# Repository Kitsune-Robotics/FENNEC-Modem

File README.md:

# The Fennec Modem

A **F**lexible **E**xperimental **N**etwork for **N**ovel **E**lectronic **C**ommunication!

Hello and thank you for looking in here!

APRN is a combined pairing of bell202 from packet radio, with SSTV and other more analog formats. While never widely adopted, I always had a strong affection for the strange format! The inspiration for this format was originally recorded [here.](https://web.archive.org/web/20080328040214/http://web.usna.navy.mil/~bruninga/aprntxt.html)

The Fennec Modem is designed with APRN in mind! But is in no means only limted to that one format, any AFSK or similar audio/soundcard mode radio should be possible with this board!

 - [x] APRN
 - [x] Packet
 - [ ] APRS
 - [ ] Other SSTV Formats

# Getting started

Clone this repo

```shell
git clone --recurse-submodules https://github.com/Kitsune-Robotics/FENNEC-Modem
```

# Thank You!

Without the resources from other hams on the internet, I don't know if i would ever get this project done!

https://github.com/handiko/Dorji-TX-Shield
http://squirrelengineering.com/arduino/dra818v-aprs-144-390mhz/

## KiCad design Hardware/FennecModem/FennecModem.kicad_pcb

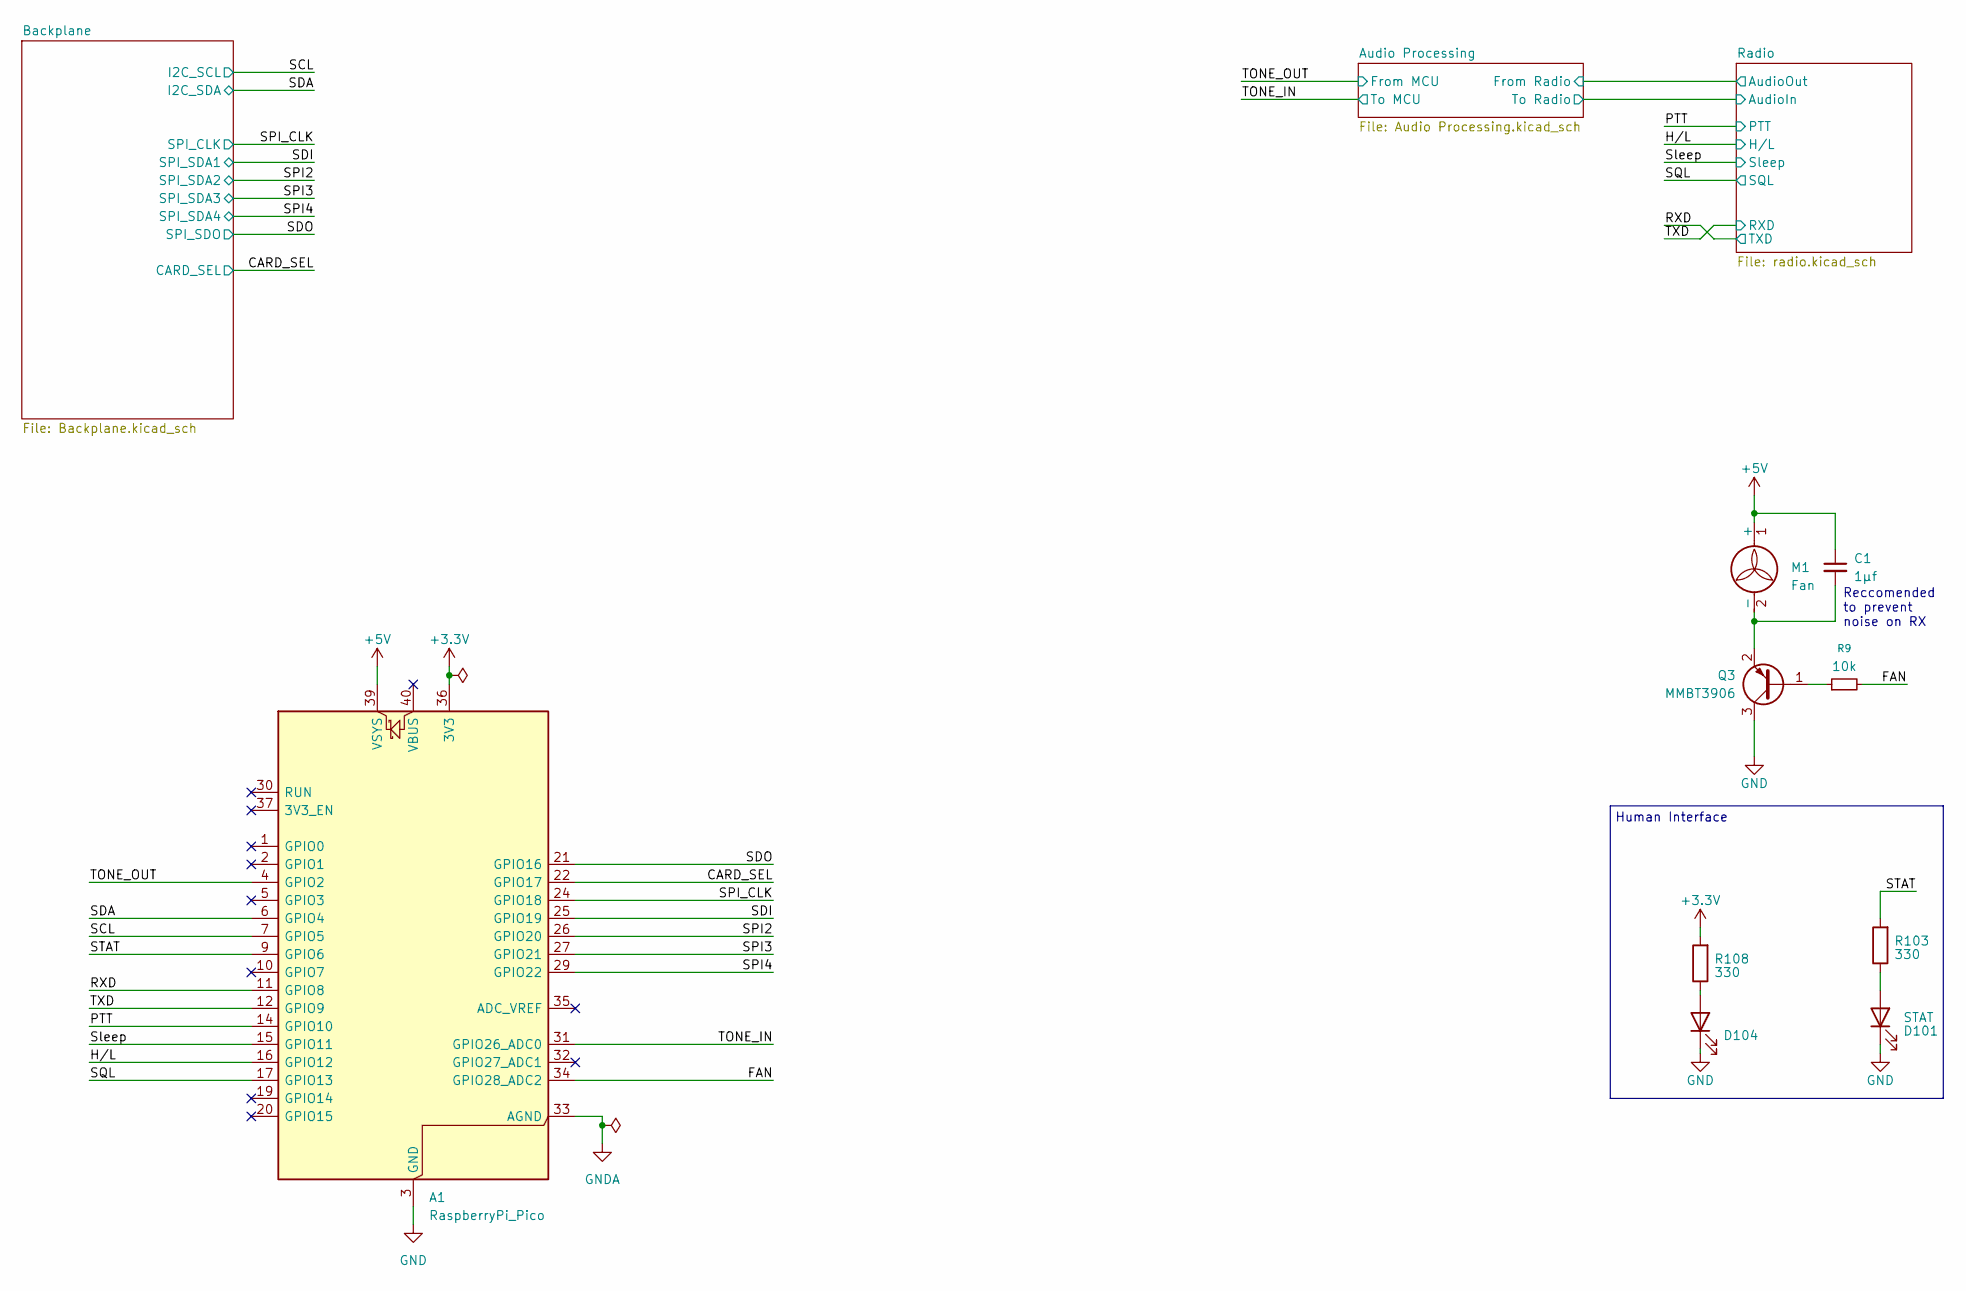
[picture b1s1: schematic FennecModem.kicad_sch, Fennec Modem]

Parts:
A1: RaspberryPi_Pico; RaspberryPi_Pico_Common_THT
C1: 1μf; C_0805_2012Metric
D101: STAT; LED_D3.0mm_Horizontal_O1.27mm_Z2.0mm
D104: PWR; LED_D3.0mm_Horizontal_O1.27mm_Z2.0mm
M1: Fan; JST_EH_B2B-EH-A_1x02_P2.50mm_Vertical
Q3: MMBT3906; SOT-23
R9: 10k; R_0805_2012Metric
R103, R108: 330; R_0805_2012Metric

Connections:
+3.3V: A1.36 (3V3), R108.2; also elsewhere on the board
+5V: A1.39 (VSYS), C1.1, M1.1 (+); also elsewhere on the board
/CARD_SEL: A1.22 (GPIO17); also elsewhere on the board
/FAN: A1.34 (GPIO28_ADC2), R9.2
/H/L: A1.16 (GPIO12); also elsewhere on the board
/PTT: A1.14 (GPIO10); also elsewhere on the board
/RXD: A1.11 (GPIO8); also elsewhere on the board
/SCL: A1.7 (GPIO5)
/SDA: A1.6 (GPIO4)
/SDI: A1.25 (GPIO19); also elsewhere on the board
/SDO: A1.21 (GPIO16); also elsewhere on the board
/SPI2: A1.26 (GPIO20); also elsewhere on the board
/SPI3: A1.27 (GPIO21); also elsewhere on the board
/SPI4: A1.29 (GPIO22); also elsewhere on the board
/SPI_CLK: A1.24 (GPIO18); also elsewhere on the board
/SQL: A1.17 (GPIO13); also elsewhere on the board
/STAT: A1.9 (GPIO6), R103.2
/Sleep: A1.15 (GPIO11); also elsewhere on the board
/TONE_IN: A1.31 (GPIO26_ADC0); also elsewhere on the board
/TONE_OUT: A1.4 (GPIO2); also elsewhere on the board
/TXD: A1.12 (GPIO9); also elsewhere on the board
GND: A1.3 (GND), A1.8 (GND), A1.13 (GND), A1.18 (GND), A1.23 (GND), A1.28 (GND), A1.38 (GND), D101.1 (K), D104.1 (K), Q3.3 (C); also elsewhere on the board
GNDA: A1.33 (AGND); also elsewhere on the board
unnamed: D101.2 (A), R103.1
unnamed: D104.2 (A), R108.1
unnamed: C1.2, M1.2 (-), Q3.2 (E)
unnamed: Q3.1 (B), R9.1

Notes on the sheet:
Reccomended to prevent noise on RX
Human Interface

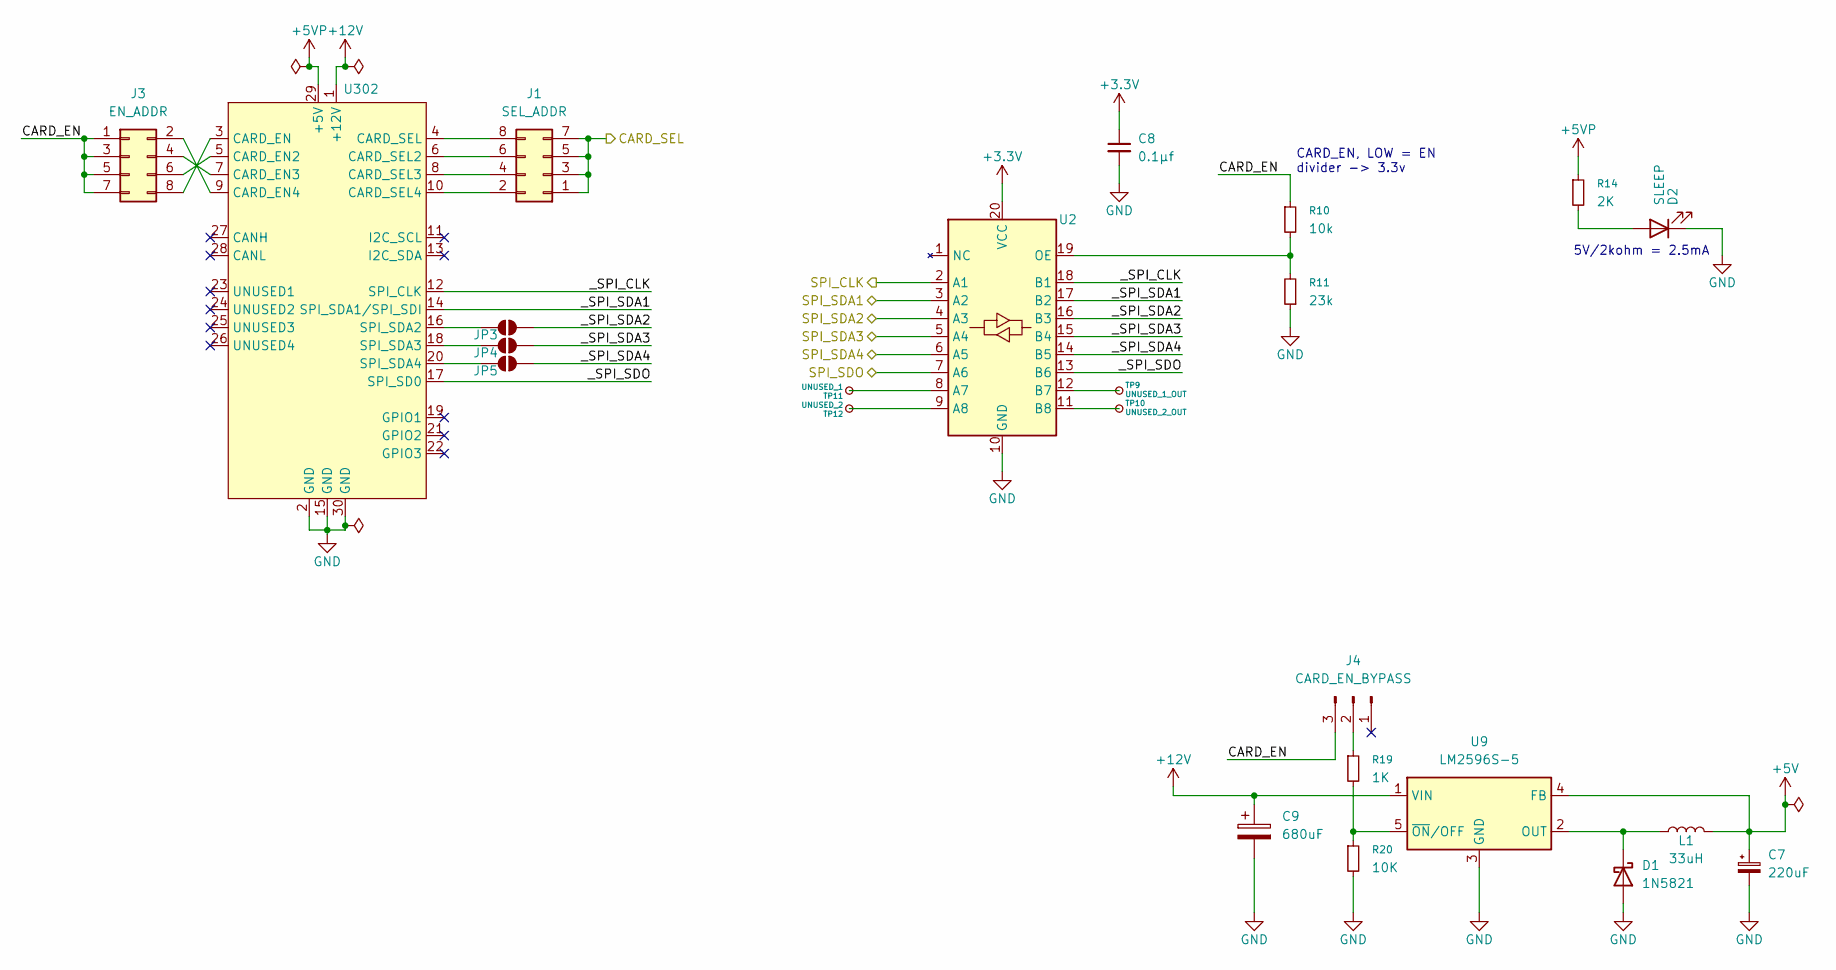
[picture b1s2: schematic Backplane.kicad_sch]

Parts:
C7: 220uF; CP_Radial_D5.0mm_P2.50mm
C8: 0.1μf; C_0805_2012Metric
C9: 680uF; CP_Radial_D10.0mm_P5.00mm
D1: 1N5821; D_DO-41_SOD81_P5.08mm_Vertical_AnodeUp; LCSC# C5295406
D2: SLEEP; LED_0805_2012Metric
J1: SEL_ADDR; PinHeader_2x04_P2.54mm_Vertical
J3: EN_ADDR; PinHeader_2x04_P2.54mm_Vertical
J4: CARD_EN_BYPASS; PinHeader_1x03_P2.54mm_Vertical
JP3, JP4, JP5: SolderJumper_2_Open; SolderJumper-2_P1.3mm_Open_TrianglePad1.0x1.5mm
L1: 33uH; L_6.3x6.3_H3
R10: 10k; R_0805_2012Metric
R11: 23k; R_0805_2012Metric
R14: 2K; R_0805_2012Metric
R19: 1K; R_0805_2012Metric
R20: 10K; R_0805_2012Metric
TP9: UNUSED_1_OUT; TestPoint_Bridge_Pitch2.0mm_Drill0.7mm
TP10: UNUSED_2_OUT; TestPoint_Bridge_Pitch2.0mm_Drill0.7mm
TP11: UNUSED_1; TestPoint_Bridge_Pitch2.0mm_Drill0.7mm
TP12: UNUSED_2; TestPoint_Bridge_Pitch2.0mm_Drill0.7mm
U2: SN74CBTLV3245A; SSOP-20_3.9x8.7mm_P0.635mm; LCSC# C2878923
U9: LM2596S-5; TO-263-5_TabPin3; LCSC# C116713
U302: Lewis_Card_Connector

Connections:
+3.3V: C8.1, U2.20 (VCC); also elsewhere on the board
+5V: C7.1, L1.2, U9.4 (FB); also elsewhere on the board
+5VP: R14.1, U302.29 (+5V)
+12V: C9.1, U9.1 (VIN), U302.1 (+12V)
/Backplane/CARD_EN: J3.1, J3.3, J3.5, J3.7, J4.3, R10.1
/Backplane/_SPI_CLK: U2.18 (B1), U302.12 (SPI_CLK)
/Backplane/_SPI_SDA1: U2.17 (B2), U302.14 (SPI_SDA1/SPI_SDI)
/Backplane/_SPI_SDA2: JP3.1 (A), U2.16 (B3)
/Backplane/_SPI_SDA3: JP4.1 (A), U2.15 (B4)
/Backplane/_SPI_SDA4: JP5.1 (A), U2.14 (B5)
/Backplane/_SPI_SDO: U2.13 (B6), U302.17 (SPI_SD0)
/CARD_SEL: J1.1, J1.3, J1.5, J1.7; also elsewhere on the board
/SDI: U2.3 (A2); also elsewhere on the board
/SDO: U2.7 (A6); also elsewhere on the board
/SPI2: U2.4 (A3); also elsewhere on the board
/SPI3: U2.5 (A4); also elsewhere on the board
/SPI4: U2.6 (A5); also elsewhere on the board
/SPI_CLK: U2.2 (A1); also elsewhere on the board
GND: C7.2, C8.2, C9.2, D1.2 (A), D2.1 (K), R11.1, R20.2, U2.10 (GND), U9.3 (GND), U302.2 (GND), U302.15 (GND), U302.30 (GND); also elsewhere on the board
unnamed: D1.1 (K), L1.1, U9.2 (OUT)
unnamed: D2.2 (A), R14.2
unnamed: J1.2, U302.10 (CARD_SEL4)
unnamed: J1.4, U302.8 (CARD_SEL3)
unnamed: J1.6, U302.6 (CARD_SEL2)
unnamed: J1.8, U302.4 (CARD_SEL)
unnamed: J3.2, U302.9 (CARD_EN4)
unnamed: J3.4, U302.7 (CARD_EN3)
unnamed: J3.6, U302.5 (CARD_EN2)
unnamed: J3.8, U302.3 (CARD_EN)
unnamed: J4.2, R19.1
unnamed: JP3.2 (B), U302.16 (SPI_SDA2)
unnamed: JP4.2 (B), U302.18 (SPI_SDA3)
unnamed: JP5.2 (B), U302.20 (SPI_SDA4)
unnamed: TP11.1, U2.8 (A7)
unnamed: TP12.1, U2.9 (A8)
unnamed: TP9.1, U2.12 (B7)
unnamed: TP10.1, U2.11 (B8)
unnamed: R10.2, R11.2, U2.19 (OE)
unnamed: R19.2, R20.1, U9.5 (~ON/OFF)

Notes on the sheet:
5V/2kohm = 2.5mA
CARD_EN, LOW = EN divider -> 3.3v

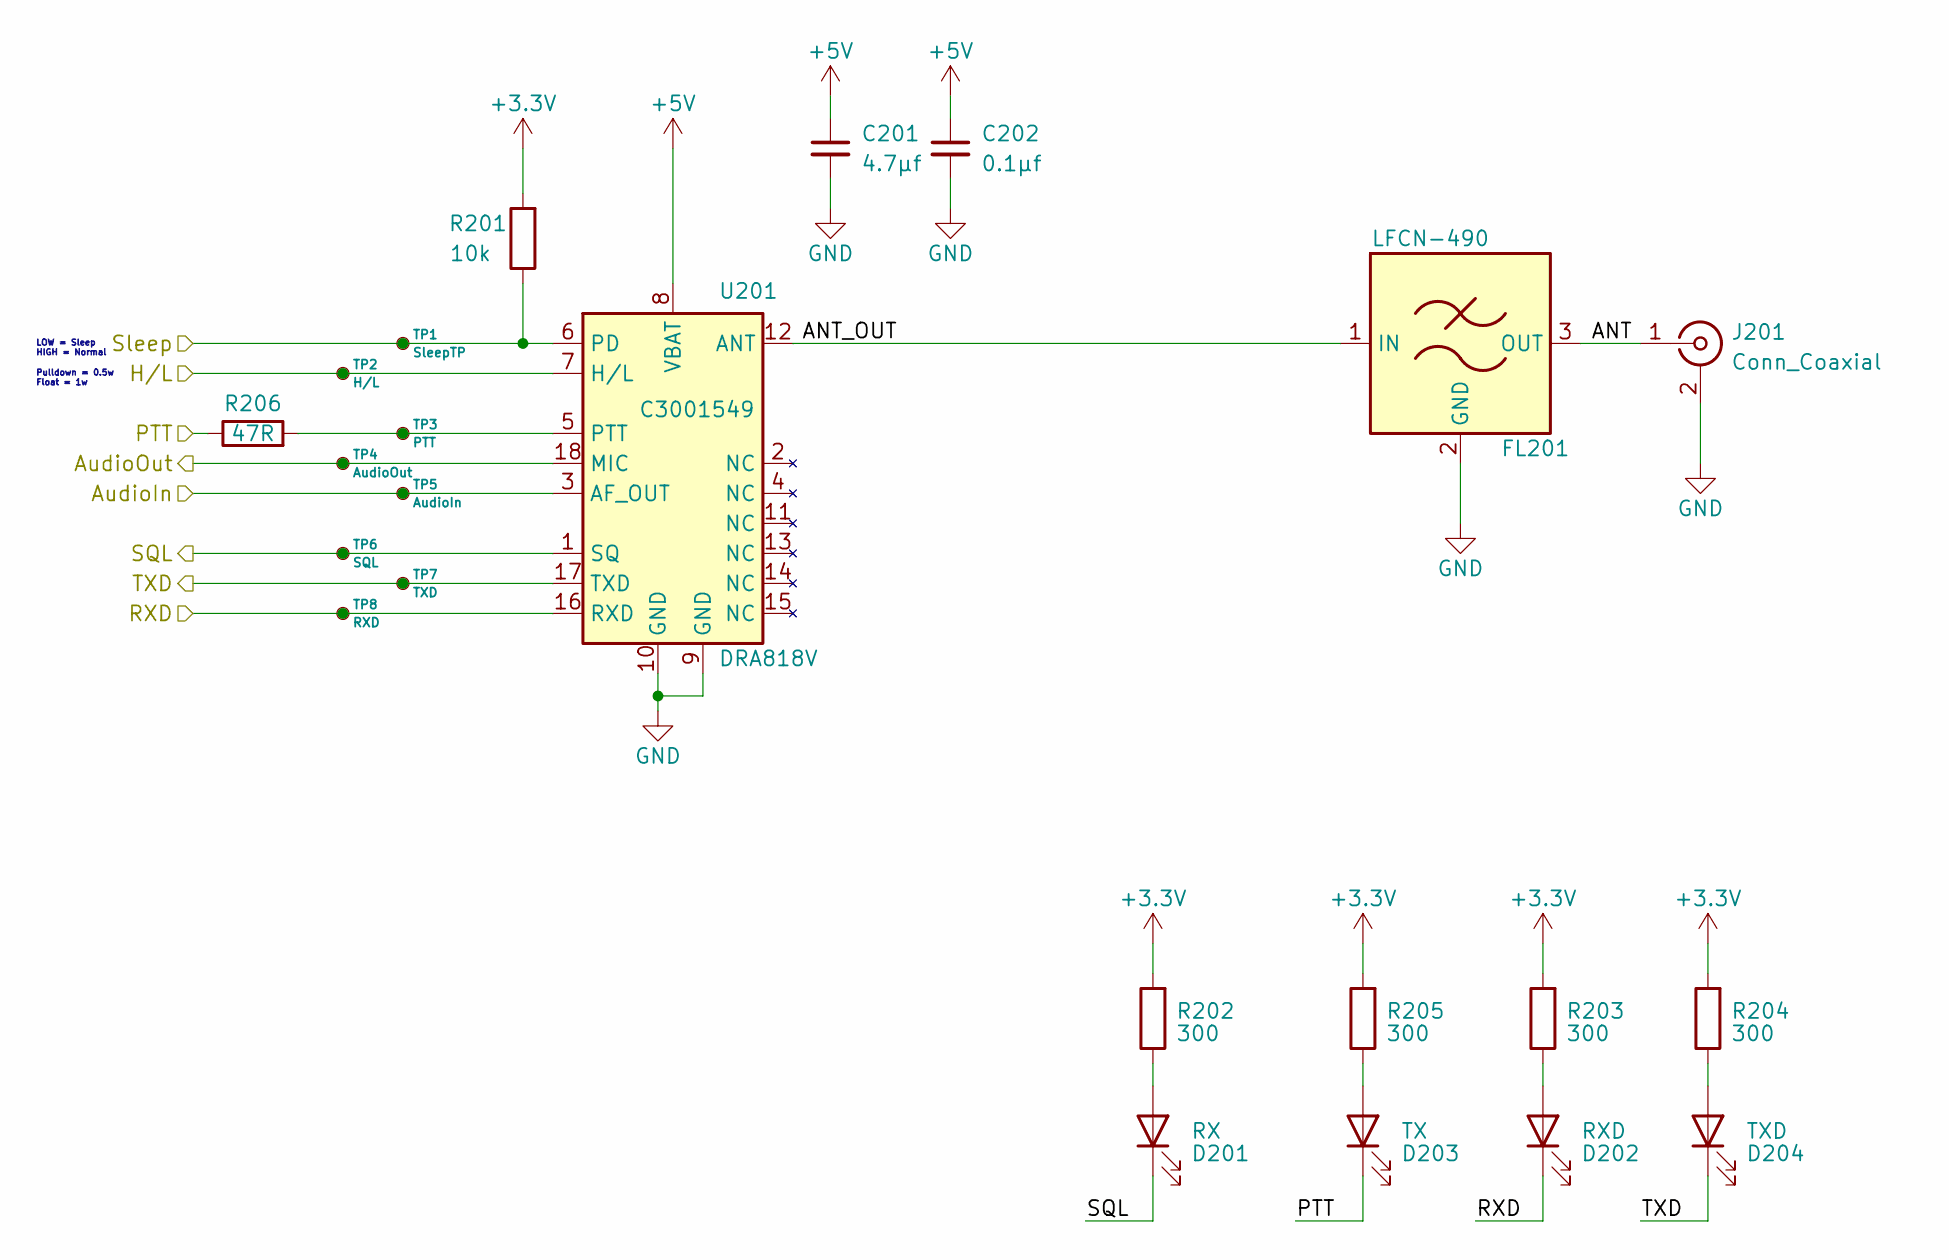
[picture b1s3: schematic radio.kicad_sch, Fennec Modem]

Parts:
C201: 4.7μf; C_0805_2012Metric
C202: 0.1μf; C_0805_2012Metric
D201: RX; LED_D3.0mm_Horizontal_O1.27mm_Z2.0mm
D202: RXD; LED_0805_2012Metric
D203: TX; LED_D3.0mm_Horizontal_O1.27mm_Z2.0mm
D204: TXD; LED_0805_2012Metric
FL201: LFCN-490; Filter_Mini-Circuits_FV1206
J201: Conn_Coaxial; SMA_Amphenol_132289_EdgeMount
R201: 10k; R_0805_2012Metric
R202, R203, R204, R205: 300; R_0805_2012Metric
R206: 47R; R_0805_2012Metric
TP1: SleepTP; TestPoint_Bridge_Pitch2.0mm_Drill0.7mm
TP2: H/L; TestPoint_Bridge_Pitch2.0mm_Drill0.7mm
TP3: PTT; TestPoint_Bridge_Pitch2.0mm_Drill0.7mm
TP4: AudioOut; TestPoint_Bridge_Pitch2.0mm_Drill0.7mm
TP5: AudioIn; TestPoint_Bridge_Pitch2.0mm_Drill0.7mm
TP6: SQL; TestPoint_Bridge_Pitch2.0mm_Drill0.7mm
TP7: TXD; TestPoint_Bridge_Pitch2.0mm_Drill0.7mm
TP8: RXD; TestPoint_Bridge_Pitch2.0mm_Drill0.7mm
U201: DRA818V; LCSC# C3001549

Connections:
+3.3V: R201.2, R202.2, R203.2, R204.2, R205.2; also elsewhere on the board
+5V: C201.1, C202.1, U201.8 (VBAT); also elsewhere on the board
/Audio Processing/From Radio: TP4.1, U201.18 (MIC); also elsewhere on the board
/Audio Processing/To Radio: TP5.1, U201.3 (AF_OUT); also elsewhere on the board
/H/L: TP2.1, U201.7 (H/L); also elsewhere on the board
/PTT: D203.1 (K), R206.1; also elsewhere on the board
/RXD: D204.1 (K), TP7.1, U201.17 (TXD); also elsewhere on the board
/Radio/ANT: FL201.3 (OUT), J201.1 (In)
/Radio/ANT_OUT: FL201.1 (IN), U201.12 (ANT)
/SQL: D201.1 (K), TP6.1, U201.1 (SQ); also elsewhere on the board
/Sleep: R201.1, TP1.1, U201.6 (PD); also elsewhere on the board
/TXD: D202.1 (K), TP8.1, U201.16 (RXD); also elsewhere on the board
GND: C201.2, C202.2, FL201.2 (GND), FL201.4 (GND), J201.2 (Ext), U201.9 (GND), U201.10 (GND); also elsewhere on the board
unnamed: D201.2 (A), R202.1
unnamed: D202.2 (A), R203.1
unnamed: D203.2 (A), R205.1
unnamed: D204.2 (A), R204.1
unnamed: R206.2, TP3.1, U201.5 (PTT)

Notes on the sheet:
Pulldown = 0.5w Float = 1w
LOW = Sleep HIGH = Normal

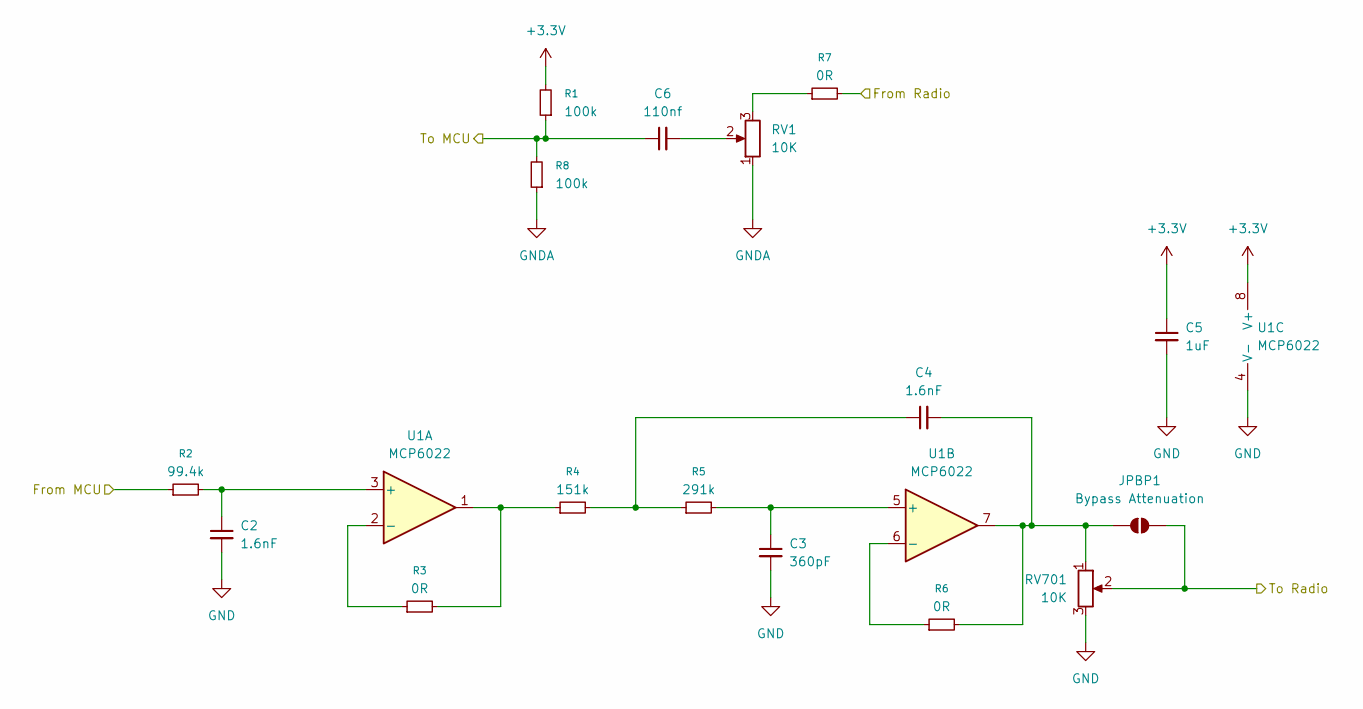
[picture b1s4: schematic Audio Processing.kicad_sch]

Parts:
C2, C4: 1.6nF; C_0805_2012Metric
C3: 360pF; C_0805_2012Metric
C5: 1uF; C_0805_2012Metric
C6: 110nf; C_0805_2012Metric
JPBP1: Bypass Attenuation; SolderJumper-2_P1.3mm_Open_TrianglePad1.0x1.5mm
R1, R8: 100k; R_0805_2012Metric
R2: 99.4k; R_0805_2012Metric
R3, R6, R7: 0R; R_0805_2012Metric
R4: 151k; R_0805_2012Metric
R5: 291k; R_0805_2012Metric
RV1, RV701: 10K; Potentiometer_Bourns_TC33X_Vertical
U1: MCP6022; SOIC-8_3.9x4.9mm_P1.27mm; LCSC# C57639

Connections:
+3.3V: C5.1, R1.2, U1.8 (V+); also elsewhere on the board
/Audio Processing/From Radio: R7.2; also elsewhere on the board
/Audio Processing/To Radio: JPBP1.2 (B), RV701.2; also elsewhere on the board
/TONE_IN: C6.1, R1.1, R8.2; also elsewhere on the board
/TONE_OUT: R2.1; also elsewhere on the board
GND: C2.2, C3.2, C5.2, RV701.3, U1.4 (V-); also elsewhere on the board
GNDA: R8.1, RV1.1; also elsewhere on the board
unnamed: C4.1, R4.2, R5.1
unnamed: C6.2, RV1.2
unnamed: C4.2, JPBP1.1 (A), R6.2, RV701.1, U1.7
unnamed: R3.2, R4.1, U1.1
unnamed: R7.1, RV1.3
unnamed: C2.1, R2.2, U1.3 (+)
unnamed: R3.1, U1.2 (-)
unnamed: C3.1, R5.2, U1.5 (+)
unnamed: R6.1, U1.6 (-)

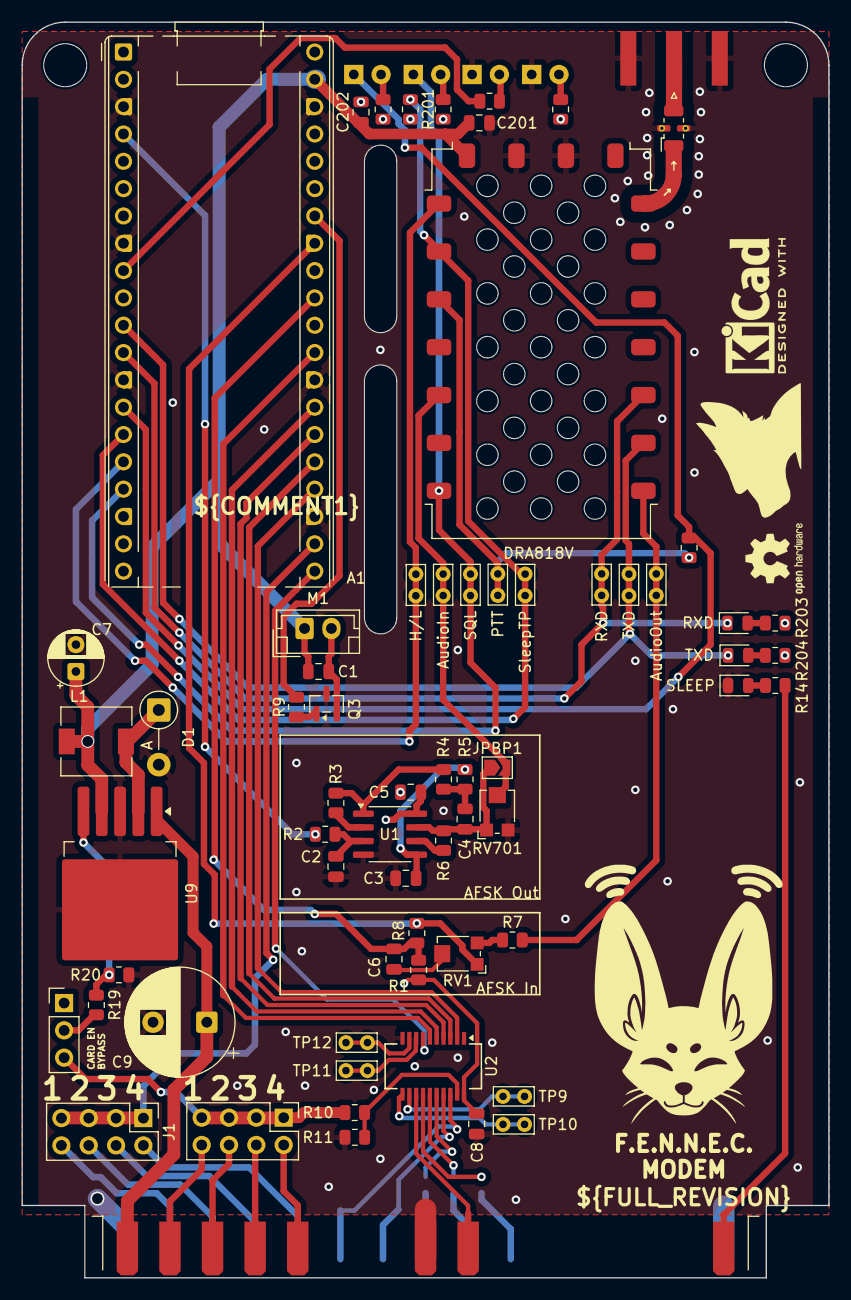
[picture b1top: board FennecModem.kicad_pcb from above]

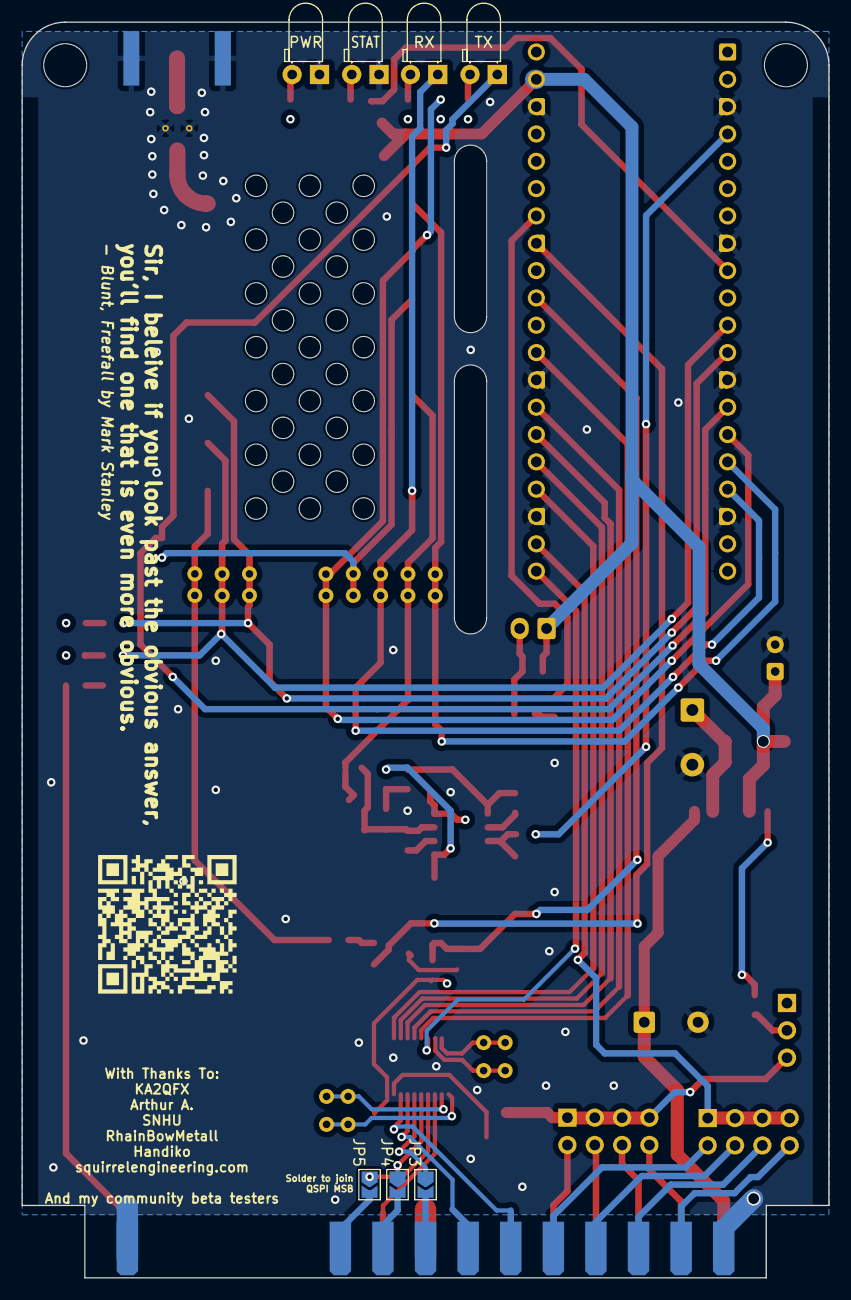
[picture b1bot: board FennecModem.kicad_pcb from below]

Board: 4 copper layers, 75.0 x 116.7 mm, 73 parts (7 on the bottom side), 72 nets.

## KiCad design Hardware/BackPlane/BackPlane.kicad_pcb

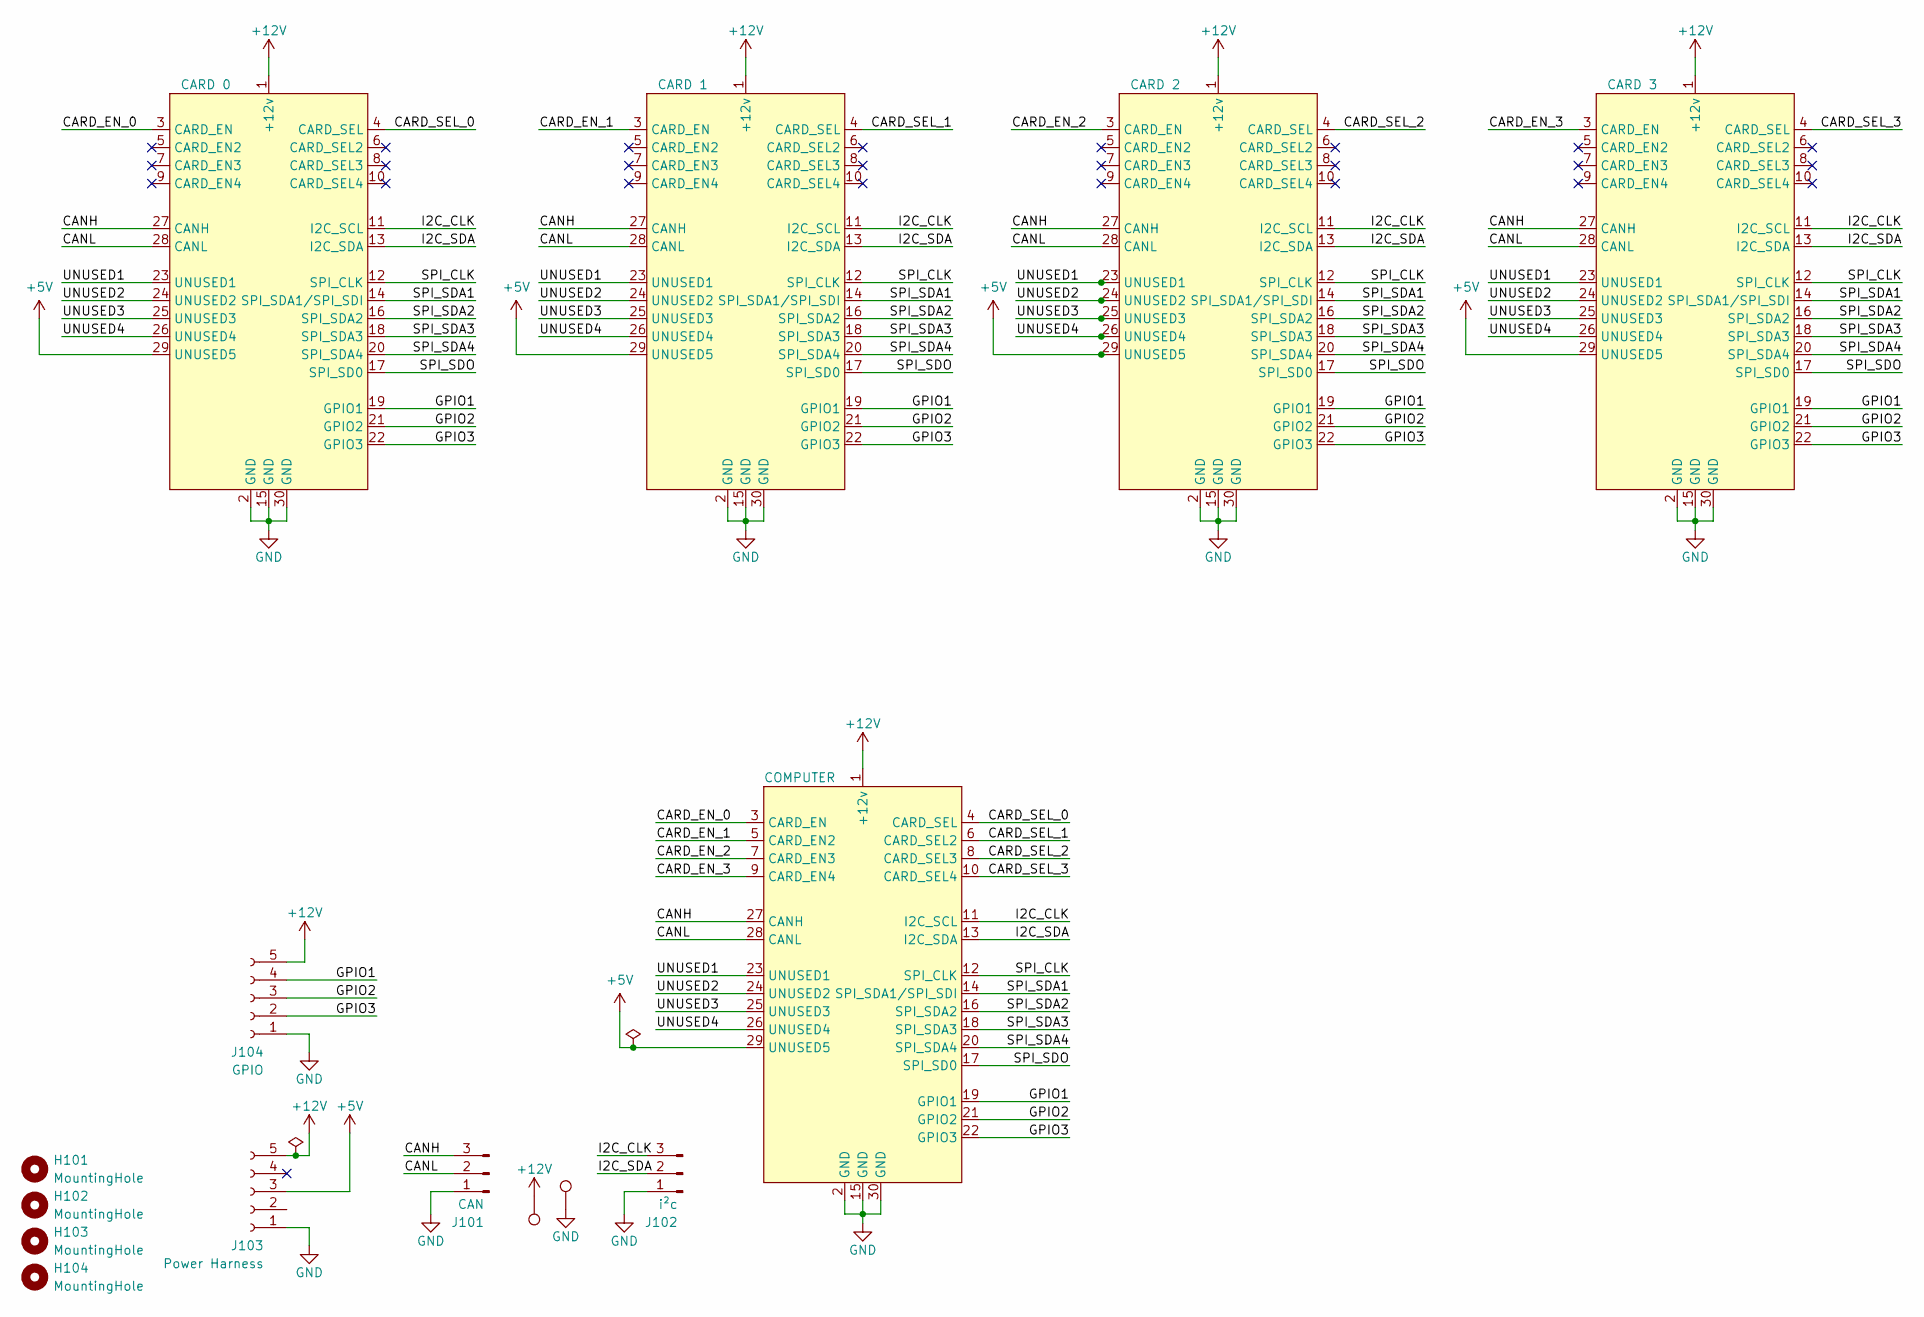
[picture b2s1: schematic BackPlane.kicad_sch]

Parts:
H101, H102, H103, H104: MountingHole; MountingHole_3.5mm
J101: CAN; JST_EH_B3B-EH-A_1x03_P2.50mm_Vertical
J102: i²c; JST_EH_B3B-EH-A_1x03_P2.50mm_Vertical
J103: Power Harness; JST_EH_B5B-EH-A_1x05_P2.50mm_Vertical
J104: GPIO; JST_EH_B5B-EH-A_1x05_P2.50mm_Vertical
TP101, TP102: TestPoint; TestPoint_Loop_D2.54mm_Drill1.5mm_Beaded
U101: COMPUTER; EBM15DSEH
U102: CARD 0; EBM15DSEH
U103: CARD 1; EBM15DSEH
U104: CARD 2; EBM15DSEH
U105: CARD 3; EBM15DSEH

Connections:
+5V: J103.3, U101.29 (UNUSED5), U102.29 (UNUSED5), U103.29 (UNUSED5), U104.29 (UNUSED5), U105.29 (UNUSED5)
+12V: J103.5, J104.5, TP101.1, U101.1 (+12v), U102.1 (+12v), U103.1 (+12v), U104.1 (+12v), U105.1 (+12v)
/CANH: J101.3, U101.27 (CANH), U102.27 (CANH), U103.27 (CANH), U104.27 (CANH), U105.27 (CANH)
/CANL: J101.2, U101.28 (CANL), U102.28 (CANL), U103.28 (CANL), U104.28 (CANL), U105.28 (CANL)
/CARD_EN_0: U101.3 (CARD_EN), U102.3 (CARD_EN)
/CARD_EN_1: U101.5 (CARD_EN2), U103.3 (CARD_EN)
/CARD_EN_2: U101.7 (CARD_EN3), U104.3 (CARD_EN)
/CARD_EN_3: U101.9 (CARD_EN4), U105.3 (CARD_EN)
/CARD_SEL_0: U101.4 (CARD_SEL), U102.4 (CARD_SEL)
/CARD_SEL_1: U101.6 (CARD_SEL2), U103.4 (CARD_SEL)
/CARD_SEL_2: U101.8 (CARD_SEL3), U104.4 (CARD_SEL)
/CARD_SEL_3: U101.10 (CARD_SEL4), U105.4 (CARD_SEL)
/GPIO1: J104.4, U101.19 (GPIO1), U102.19 (GPIO1), U103.19 (GPIO1), U104.19 (GPIO1), U105.19 (GPIO1)
/GPIO2: J104.3, U101.21 (GPIO2), U102.21 (GPIO2), U103.21 (GPIO2), U104.21 (GPIO2), U105.21 (GPIO2)
/GPIO3: J104.2, U101.22 (GPIO3), U102.22 (GPIO3), U103.22 (GPIO3), U104.22 (GPIO3), U105.22 (GPIO3)
/I2C_CLK: J102.3, U101.11 (I2C_SCL), U102.11 (I2C_SCL), U103.11 (I2C_SCL), U104.11 (I2C_SCL), U105.11 (I2C_SCL)
/I2C_SDA: J102.2, U101.13 (I2C_SDA), U102.13 (I2C_SDA), U103.13 (I2C_SDA), U104.13 (I2C_SDA), U105.13 (I2C_SDA)
/SPI_CLK: U101.12 (SPI_CLK), U102.12 (SPI_CLK), U103.12 (SPI_CLK), U104.12 (SPI_CLK), U105.12 (SPI_CLK)
/SPI_SDA1: U101.14 (SPI_SDA1/SPI_SDI), U102.14 (SPI_SDA1/SPI_SDI), U103.14 (SPI_SDA1/SPI_SDI), U104.14 (SPI_SDA1/SPI_SDI), U105.14 (SPI_SDA1/SPI_SDI)
/SPI_SDA2: U101.16 (SPI_SDA2), U102.16 (SPI_SDA2), U103.16 (SPI_SDA2), U104.16 (SPI_SDA2), U105.16 (SPI_SDA2)
/SPI_SDA3: U101.18 (SPI_SDA3), U102.18 (SPI_SDA3), U103.18 (SPI_SDA3), U104.18 (SPI_SDA3), U105.18 (SPI_SDA3)
/SPI_SDA4: U101.20 (SPI_SDA4), U102.20 (SPI_SDA4), U103.20 (SPI_SDA4), U104.20 (SPI_SDA4), U105.20 (SPI_SDA4)
/SPI_SDO: U101.17 (SPI_SD0), U102.17 (SPI_SD0), U103.17 (SPI_SD0), U104.17 (SPI_SD0), U105.17 (SPI_SD0)
/UNUSED1: U101.23 (UNUSED1), U102.23 (UNUSED1), U103.23 (UNUSED1), U104.23 (UNUSED1), U105.23 (UNUSED1)
/UNUSED2: U101.24 (UNUSED2), U102.24 (UNUSED2), U103.24 (UNUSED2), U104.24 (UNUSED2), U105.24 (UNUSED2)
/UNUSED3: U101.25 (UNUSED3), U102.25 (UNUSED3), U103.25 (UNUSED3), U104.25 (UNUSED3), U105.25 (UNUSED3)
/UNUSED4: U101.26 (UNUSED4), U102.26 (UNUSED4), U103.26 (UNUSED4), U104.26 (UNUSED4), U105.26 (UNUSED4)
GND: J101.1, J102.1, J103.1, J104.1, TP102.1, U101.2 (GND), U101.15 (GND), U101.30 (GND), U102.2 (GND), U102.15 (GND), U102.30 (GND), U103.2 (GND), U103.15 (GND), U103.30 (GND), U104.2 (GND), U104.15 (GND), U104.30 (GND), U105.2 (GND), U105.15 (GND), U105.30 (GND)

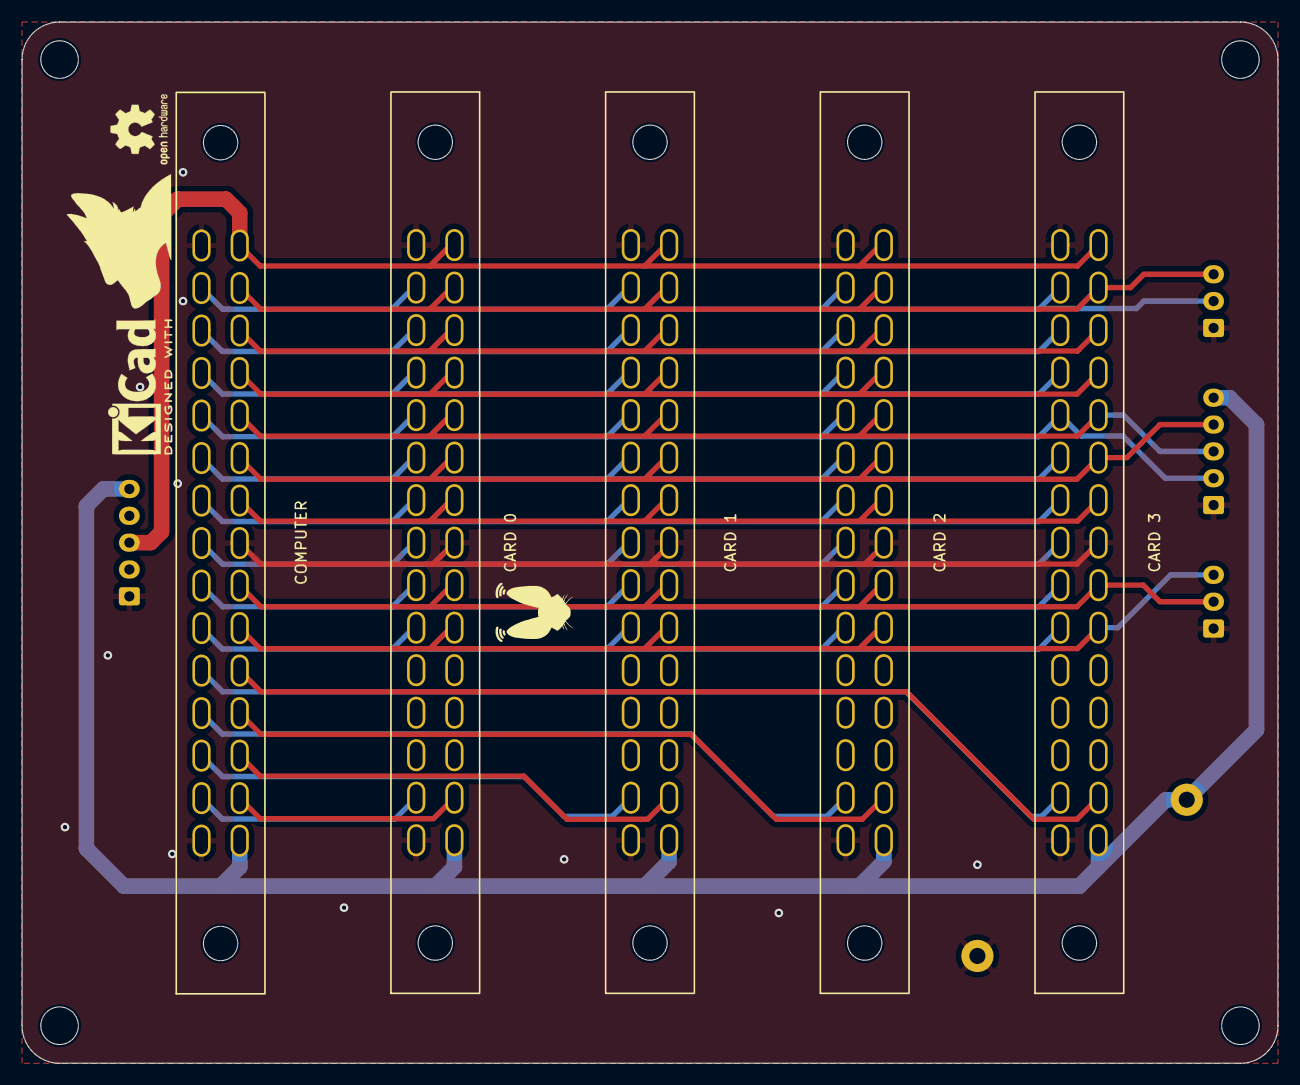
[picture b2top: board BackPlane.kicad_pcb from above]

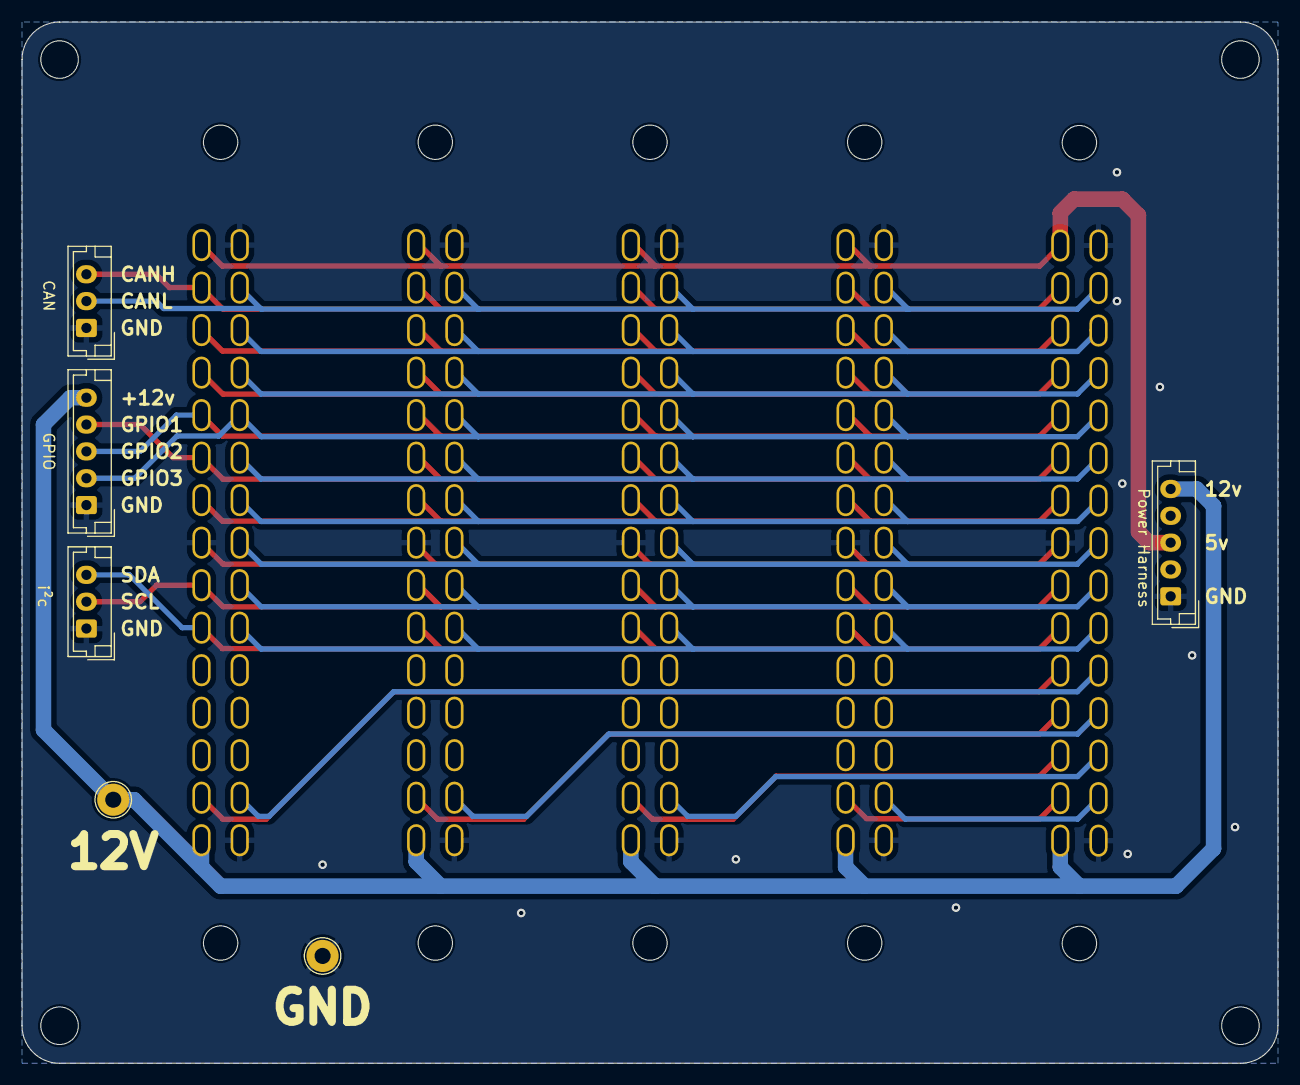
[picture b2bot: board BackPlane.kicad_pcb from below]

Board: 2 copper layers, 117.0 x 97.0 mm, 15 parts (6 on the bottom side), 28 nets.
